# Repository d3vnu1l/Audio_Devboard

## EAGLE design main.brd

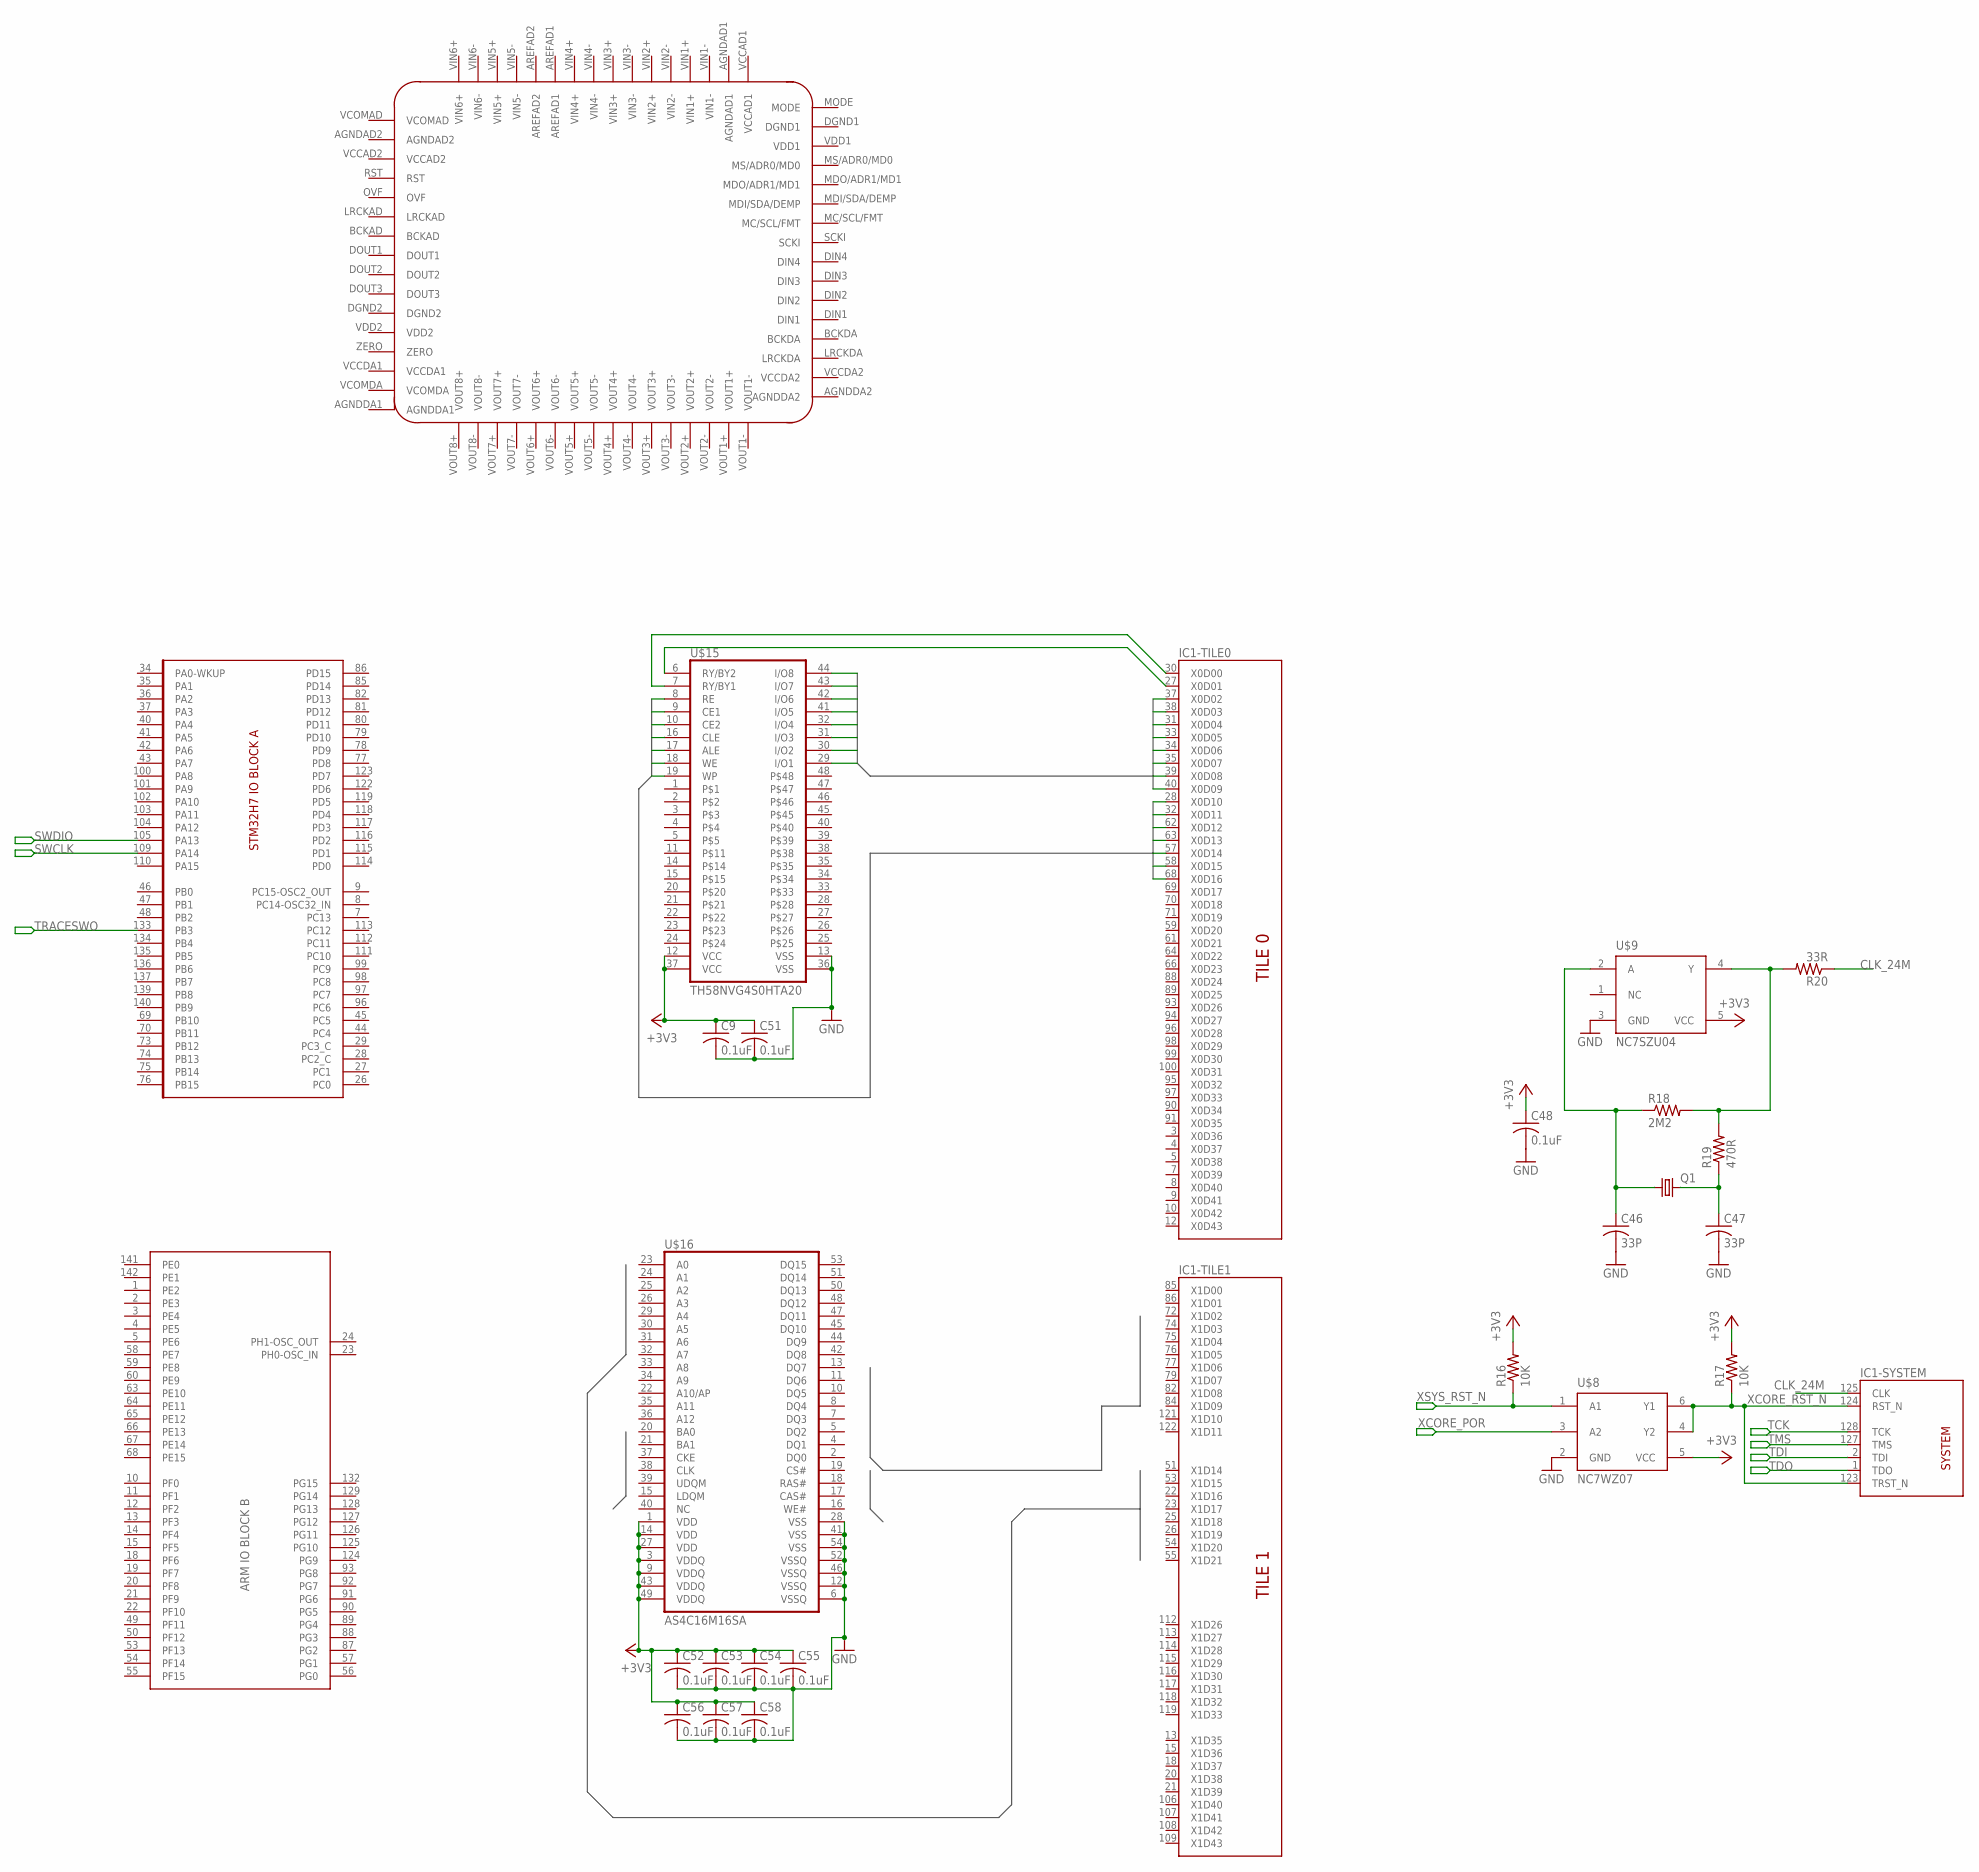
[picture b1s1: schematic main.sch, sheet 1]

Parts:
C9, C48, C51, C52, C53, C54, C55, C56, C57, C58: 0.1uF; C0603
C46, C47: 33P; C0603
IC1: XE216-TQ128; TQ128
Q1: CRYSTALSM49; SM49
R16, R17: 10K; R0603
R18: 2M2; R0603
R19: 470R; R0603
R20: 33R; R0603
U$1: STM32H7_MODULARIZED; LQFP144
U$3: PCM3168A; QFN-64-9X9MM
U$8: NC7WZ07; SC70-6L
U$9: NC7SZU04; SC70-5L
U$15: TH58NVG4S0HTA20; TSOP48
U$16: AS4C16M16SA; TSOPII-54

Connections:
+3V3: C9.1, C48.1, C51.1, C52.1, C53.1, C54.1, C55.1, C56.1, C57.1, C58.1, R16.2, R17.2, U$8.5 (VCC), U$9.5 (VCC), U$15.12 (VCC), U$15.37 (VCC), U$16.1 (VDD), U$16.3 (VDDQ), U$16.9 (VDDQ), U$16.14 (VDD), U$16.27 (VDD), U$16.43 (VDDQ), U$16.49 (VDDQ); also elsewhere on the board
ALE: IC1.57 (X0D14), U$15.17 (ALE)
CE1: IC1.32 (X0D11), U$15.9 (CE1)
CE2: IC1.62 (X0D12), U$15.10 (CE2)
CLE: IC1.63 (X0D13), U$15.16 (CLE)
CLK_24M: IC1.125 (CLK), R20.1
FLASH_BUS1: IC1.37 (X0D02), U$15.29 (I/O1)
FLASH_BUS2: IC1.38 (X0D03), U$15.30 (I/O2)
FLASH_BUS3: IC1.31 (X0D04), U$15.31 (I/O3)
FLASH_BUS4: IC1.33 (X0D05), U$15.32 (I/O4)
FLASH_BUS5: IC1.34 (X0D06), U$15.41 (I/O5)
FLASH_BUS6: IC1.35 (X0D07), U$15.42 (I/O6)
FLASH_BUS7: IC1.39 (X0D08), U$15.43 (I/O7)
FLASH_BUS8: IC1.40 (X0D09), U$15.44 (I/O8)
GND: C9.2, C46.2, C47.2, C48.2, C51.2, C52.2, C53.2, C54.2, C55.2, C56.2, C57.2, C58.2, U$8.2 (GND), U$9.3 (GND), U$15.13 (VSS), U$15.36 (VSS), U$16.6 (VSSQ), U$16.12 (VSSQ), U$16.28 (VSS), U$16.41 (VSS), U$16.46 (VSSQ), U$16.52 (VSSQ), U$16.54 (VSS); also elsewhere on the board
unnamed: C46.1, Q1.1, R18.1, U$9.2 (A)
unnamed: R18.2, R19.2, R20.2, U$9.4 (Y)
unnamed: C47.1, Q1.2, R19.1
unnamed: IC1.27 (X0D01), U$15.6 (RY/BY2)
unnamed: IC1.30 (X0D00), U$15.7 (RY/BY1)
RE: IC1.28 (X0D10), U$15.8 (RE)
SWCLK: U$1.109 (PA14); also elsewhere on the board
SWDIO: U$1.105 (PA13); also elsewhere on the board
TCK: IC1.128 (TCK); also elsewhere on the board
TDI: IC1.2 (TDI); also elsewhere on the board
TDO: IC1.1 (TDO); also elsewhere on the board
TMS: IC1.127 (TMS); also elsewhere on the board
TRACESWO: U$1.133 (PB3); also elsewhere on the board
WE: IC1.58 (X0D15), U$15.18 (WE)
WP: IC1.68 (X0D16), U$15.19 (WP)
XCORE_POR: U$8.3 (A2); also elsewhere on the board
XCORE_RST_N: IC1.123 (TRST_N), IC1.124 (RST_N), R17.1, U$8.4 (Y2), U$8.6 (Y1)
XSYS_RST_N: R16.1, U$8.1 (A1); also elsewhere on the board

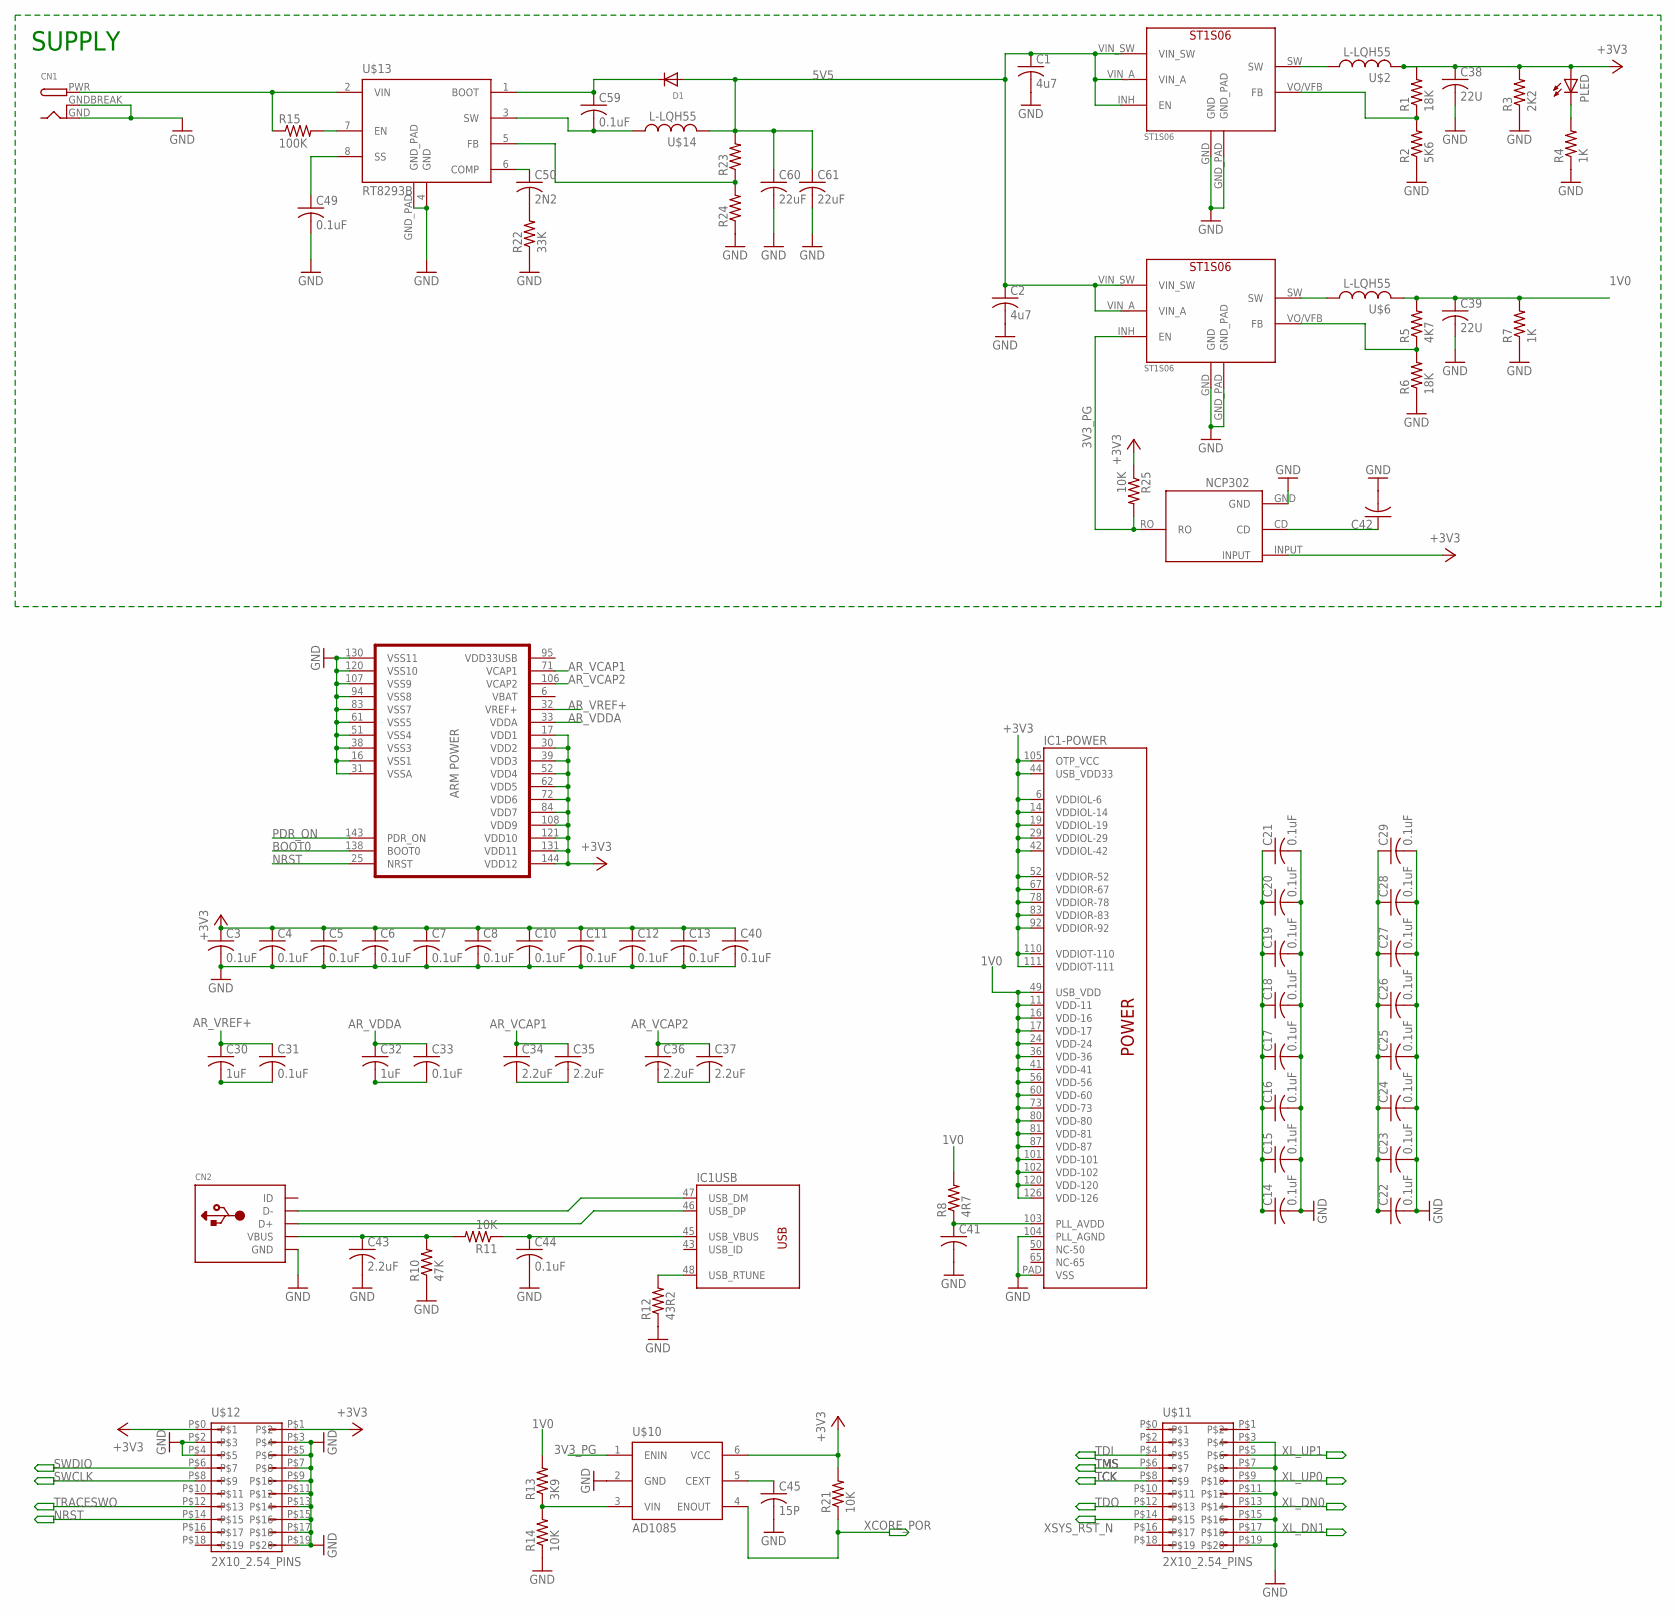
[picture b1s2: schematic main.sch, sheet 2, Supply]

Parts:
C1, C2: 4u7; C1206
C3, C4, C5, C6, C7, C8, C10, C11, C12, C13, C14, C15, C16, C17, C18, C19, C20, C21, C22, C23, C24, C25, C26, C27, C28, C29, C31, C33, C40, C44, C49, C59: 0.1uF; C0603
C30, C32: 1uF; C0603
C34, C35, C36, C37, C43: 2.2uF; C1206
C38, C39: 22U; C1206
C41, C42: C-USC0603; C0603
C45: 15P; C0603
C50: 2N2; C0603
C60, C61: 22uF; C1206
CN1: DCBARRELPTH; DCJACK_2MM_PTH
CN2: USBMINIB; USB-MINIB
D1: DIODESMA; SMADIODE
IC1: XE216-TQ128; TQ128
PLED: LEDCHIPLED_1206; CHIPLED_1206
R1, R6: 18K; R0603
R2: 5K6; R0603
R3: 2K2; R0603
R4, R7: 1K; R0603
R5: 4K7; R0603
R8: 4R7; R0603
R10: 47K; R0603
R11, R14, R21, R25: 10K; R0603
R12: 43R2; R0603
R13: 3K9; R0603
R15: 100K; R0603
R22: 33K; R0603
R23, R24: R-US_R0603; R0603
U$1: STM32H7_MODULARIZED; LQFP144
U$2, U$6, U$14: L-LQH55; LQH55
U$4, U$5: ST1S06; DFN-6
U$7: NCP302
U$10: AD1085; SC70-6L
U$11, U$12: 2X10_2.54_PINS; 2X10_2.54
U$13: RT8293B; SO-08-EP

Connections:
1V0: C39.1, IC1.11 (VDD-11), IC1.16 (VDD-16), IC1.17 (VDD-17), IC1.24 (VDD-24), IC1.36 (VDD-36), IC1.41 (VDD-41), IC1.49 (USB_VDD), IC1.56 (VDD-56), IC1.60 (VDD-60), IC1.73 (VDD-73), IC1.80 (VDD-80), IC1.81 (VDD-81), IC1.87 (VDD-87), IC1.101 (VDD-101), IC1.102 (VDD-102), IC1.120 (VDD-120), IC1.126 (VDD-126), R5.2, R7.2, R8.2, R13.2, U$6.2
3V3_PG: R25.2, U$5.INH (EN), U$7.RO, U$10.1 (ENIN)
5V5: C1.1, C2.1, C60.1, C61.1, D1.A, R23.2, U$4.INH (EN), U$4.VIN_A, U$4.VIN_SW, U$5.VIN_A, U$5.VIN_SW, U$14.2
+3V3: C3.1, C4.1, C5.1, C6.1, C7.1, C8.1, C10.1, C11.1, C12.1, C13.1, C38.1, C40.1, IC1.6 (VDDIOL-6), IC1.14 (VDDIOL-14), IC1.19 (VDDIOL-19), IC1.29 (VDDIOL-29), IC1.42 (VDDIOL-42), IC1.44 (USB_VDD33), IC1.52 (VDDIOR-52), IC1.67 (VDDIOR-67), IC1.78 (VDDIOR-78), IC1.83 (VDDIOR-83), IC1.92 (VDDIOR-92), IC1.105 (OTP_VCC), IC1.110 (VDDIOT-110), IC1.111 (VDDIOT-111), PLED.A, R1.2, R3.2, R21.2, R25.1, U$1.17 (VDD1), U$1.30 (VDD2), U$1.39 (VDD3), U$1.52 (VDD4), U$1.62 (VDD5), U$1.72 (VDD6), U$1.84 (VDD7), U$1.108 (VDD9), U$1.121 (VDD10), U$1.131 (VDD11), U$1.144 (VDD12), U$2.2, U$7.INPUT, U$10.6 (VCC), U$12.P$0, U$12.P$1; also elsewhere on the board
AR_VCAP1: C34.1, C35.1, U$1.71 (VCAP1)
AR_VCAP2: C36.1, C37.1, U$1.106 (VCAP2)
AR_VDDA: C32.1, C33.1, U$1.33 (VDDA)
AR_VREF+: C30.1, C31.1, U$1.32 (VREF+)
BOOT: C59.1, D1.C, U$13.1 (BOOT)
BOOT0: U$1.138 (BOOT0)
COMP: C50.1, U$13.6 (COMP)
EN: R15.2, U$13.7 (EN)
FB: R23.1, R24.2, U$13.5 (FB)
GND: C1.2, C2.2, C3.2, C4.2, C5.2, C6.2, C7.2, C8.2, C10.2, C11.2, C12.2, C13.2, C14.2, C15.2, C16.2, C17.2, C18.2, C19.2, C20.2, C21.2, C22.2, C23.2, C24.2, C25.2, C26.2, C27.2, C28.2, C29.2, C38.2, C39.2, C40.2, C41.2, C42.2, C43.2, C44.2, C45.2, C49.2, C60.2, C61.2, CN1.GND, CN1.GNDBREAK, CN2.GND, IC1.104 (PLL_AGND), IC1.PAD (VSS), R2.1, R3.1, R4.1, R6.1, R7.1, R10.1, R12.1, R14.1, R22.1, R24.1, U$1.16 (VSS1), U$1.31 (VSSA), U$1.38 (VSS3), U$1.51 (VSS4), U$1.61 (VSS5), U$1.83 (VSS7), U$1.94 (VSS8), U$1.107 (VSS9), U$1.120 (VSS10), U$1.130 (VSS11), U$4.GND, U$4.GND_PAD, U$5.GND, U$5.GND_PAD, U$7.GND, U$10.2 (GND), U$11.P$3, U$11.P$7, U$11.P$11, U$11.P$15, U$11.P$19, U$12.P$2, U$12.P$3, U$12.P$4, U$12.P$5, U$12.P$7, U$12.P$9, U$12.P$11, U$12.P$13, U$12.P$15, U$12.P$17, U$12.P$19, U$13.4 (GND), U$13.GND_PAD; also elsewhere on the board
unnamed: C14.1, C15.1, C16.1, C17.1, C18.1, C19.1, C20.1, C21.1
unnamed: C41.1, IC1.103 (PLL_AVDD), R8.1
unnamed: C42.1, U$7.CD
unnamed: C43.1, CN2.VBUS, R10.2, R11.2
unnamed: C34.2, C35.2
unnamed: C22.1, C23.1, C24.1, C25.1, C26.1, C27.1, C28.1, C29.1
unnamed: C36.2, C37.2
unnamed: C44.1, IC1.45 (USB_VBUS), R11.1
unnamed: C32.2, C33.2
unnamed: C30.2, C31.2
unnamed: IC1.48 (USB_RTUNE), R12.2
unnamed: CN2.D+, IC1.46 (USB_DP)
unnamed: CN2.D-, IC1.47 (USB_DM)
unnamed: PLED.C, R4.2
unnamed: R1.1, R2.2, U$4.VO/VFB (FB)
unnamed: R5.1, R6.2, U$5.VO/VFB (FB)
unnamed: U$2.1, U$4.SW
unnamed: U$5.SW, U$6.1
unnamed: R13.1, R14.2, U$10.3 (VIN)
unnamed: C45.1, U$10.5 (CEXT)
unnamed: C50.2, R22.2
NRST: U$1.25 (NRST), U$12.P$14
PDR_ON: U$1.143 (PDR_ON)
PWR: CN1.PWR, R15.1, U$13.2 (VIN)
SS: C49.1, U$13.8 (SS)
SW: C59.2, U$13.3 (SW), U$14.1
SWCLK: U$12.P$8; also elsewhere on the board
SWDIO: U$12.P$6; also elsewhere on the board
TCK: U$11.P$8; also elsewhere on the board
TDI: U$11.P$4; also elsewhere on the board
TDO: U$11.P$12; also elsewhere on the board
TMS: U$11.P$6; also elsewhere on the board
TRACESWO: U$12.P$12; also elsewhere on the board
XCORE_POR: R21.1, U$10.4 (ENOUT); also elsewhere on the board
XL_DN0: U$11.P$13
XL_DN1: U$11.P$17
XL_UP0: U$11.P$9
XL_UP1: U$11.P$5
XSYS_RST_N: U$11.P$14; also elsewhere on the board

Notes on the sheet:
SUPPLY

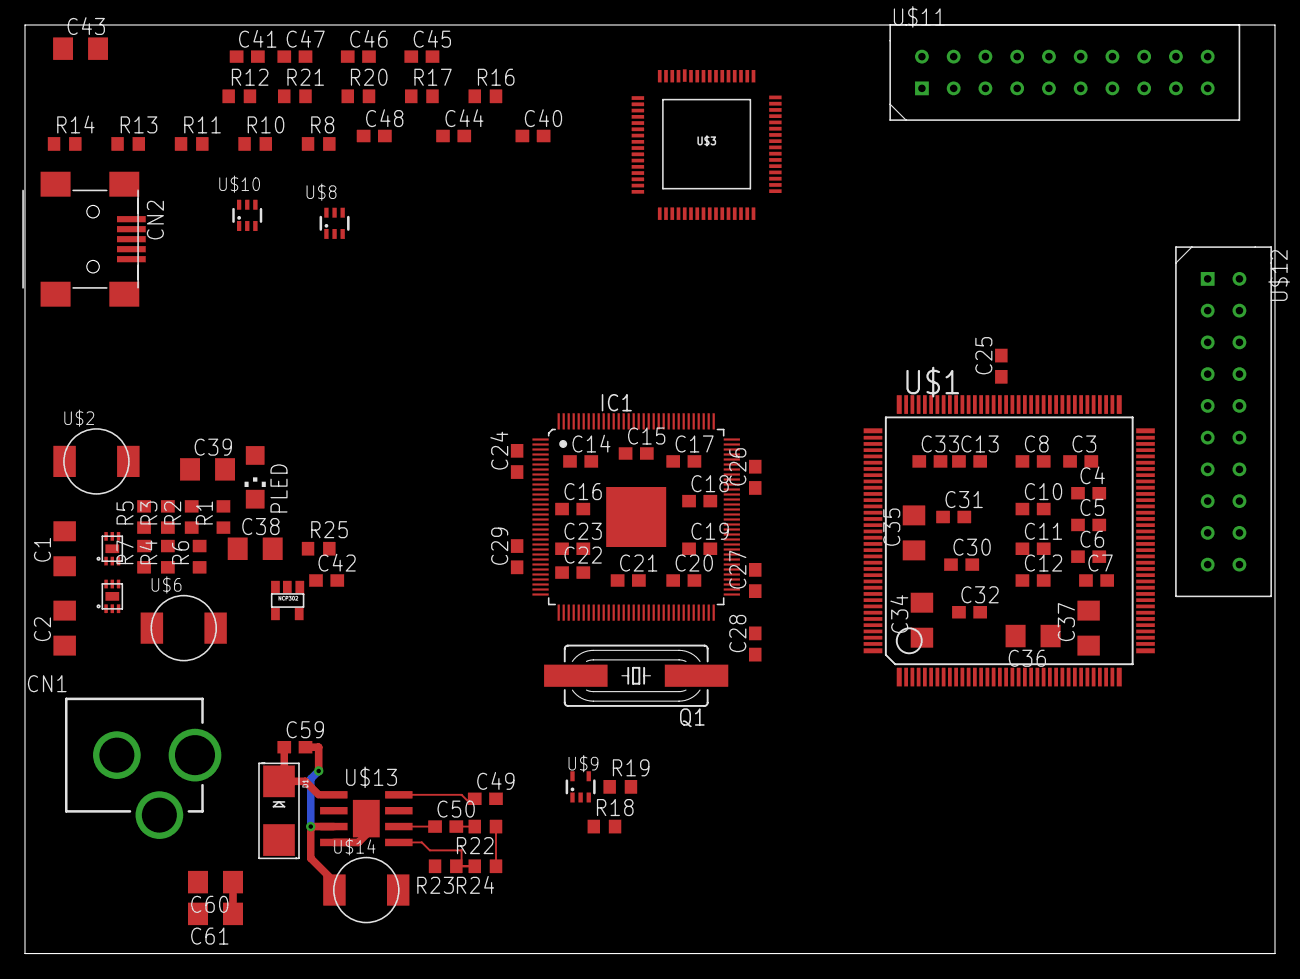
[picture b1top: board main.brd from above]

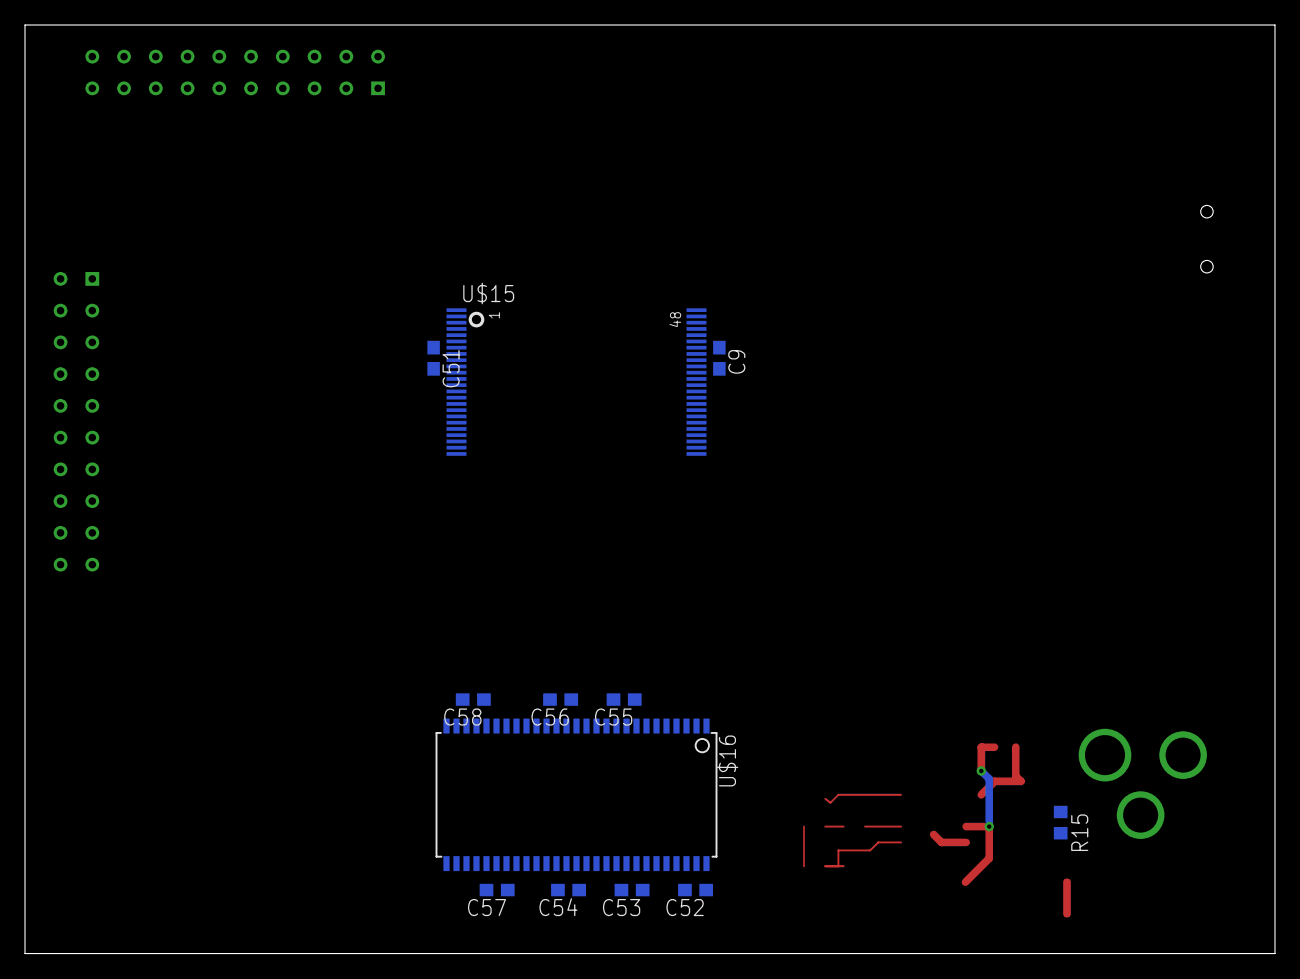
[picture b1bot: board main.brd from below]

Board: 2 copper layers, 100.0 x 74.3 mm, 107 parts (12 on the bottom side), 69 nets.

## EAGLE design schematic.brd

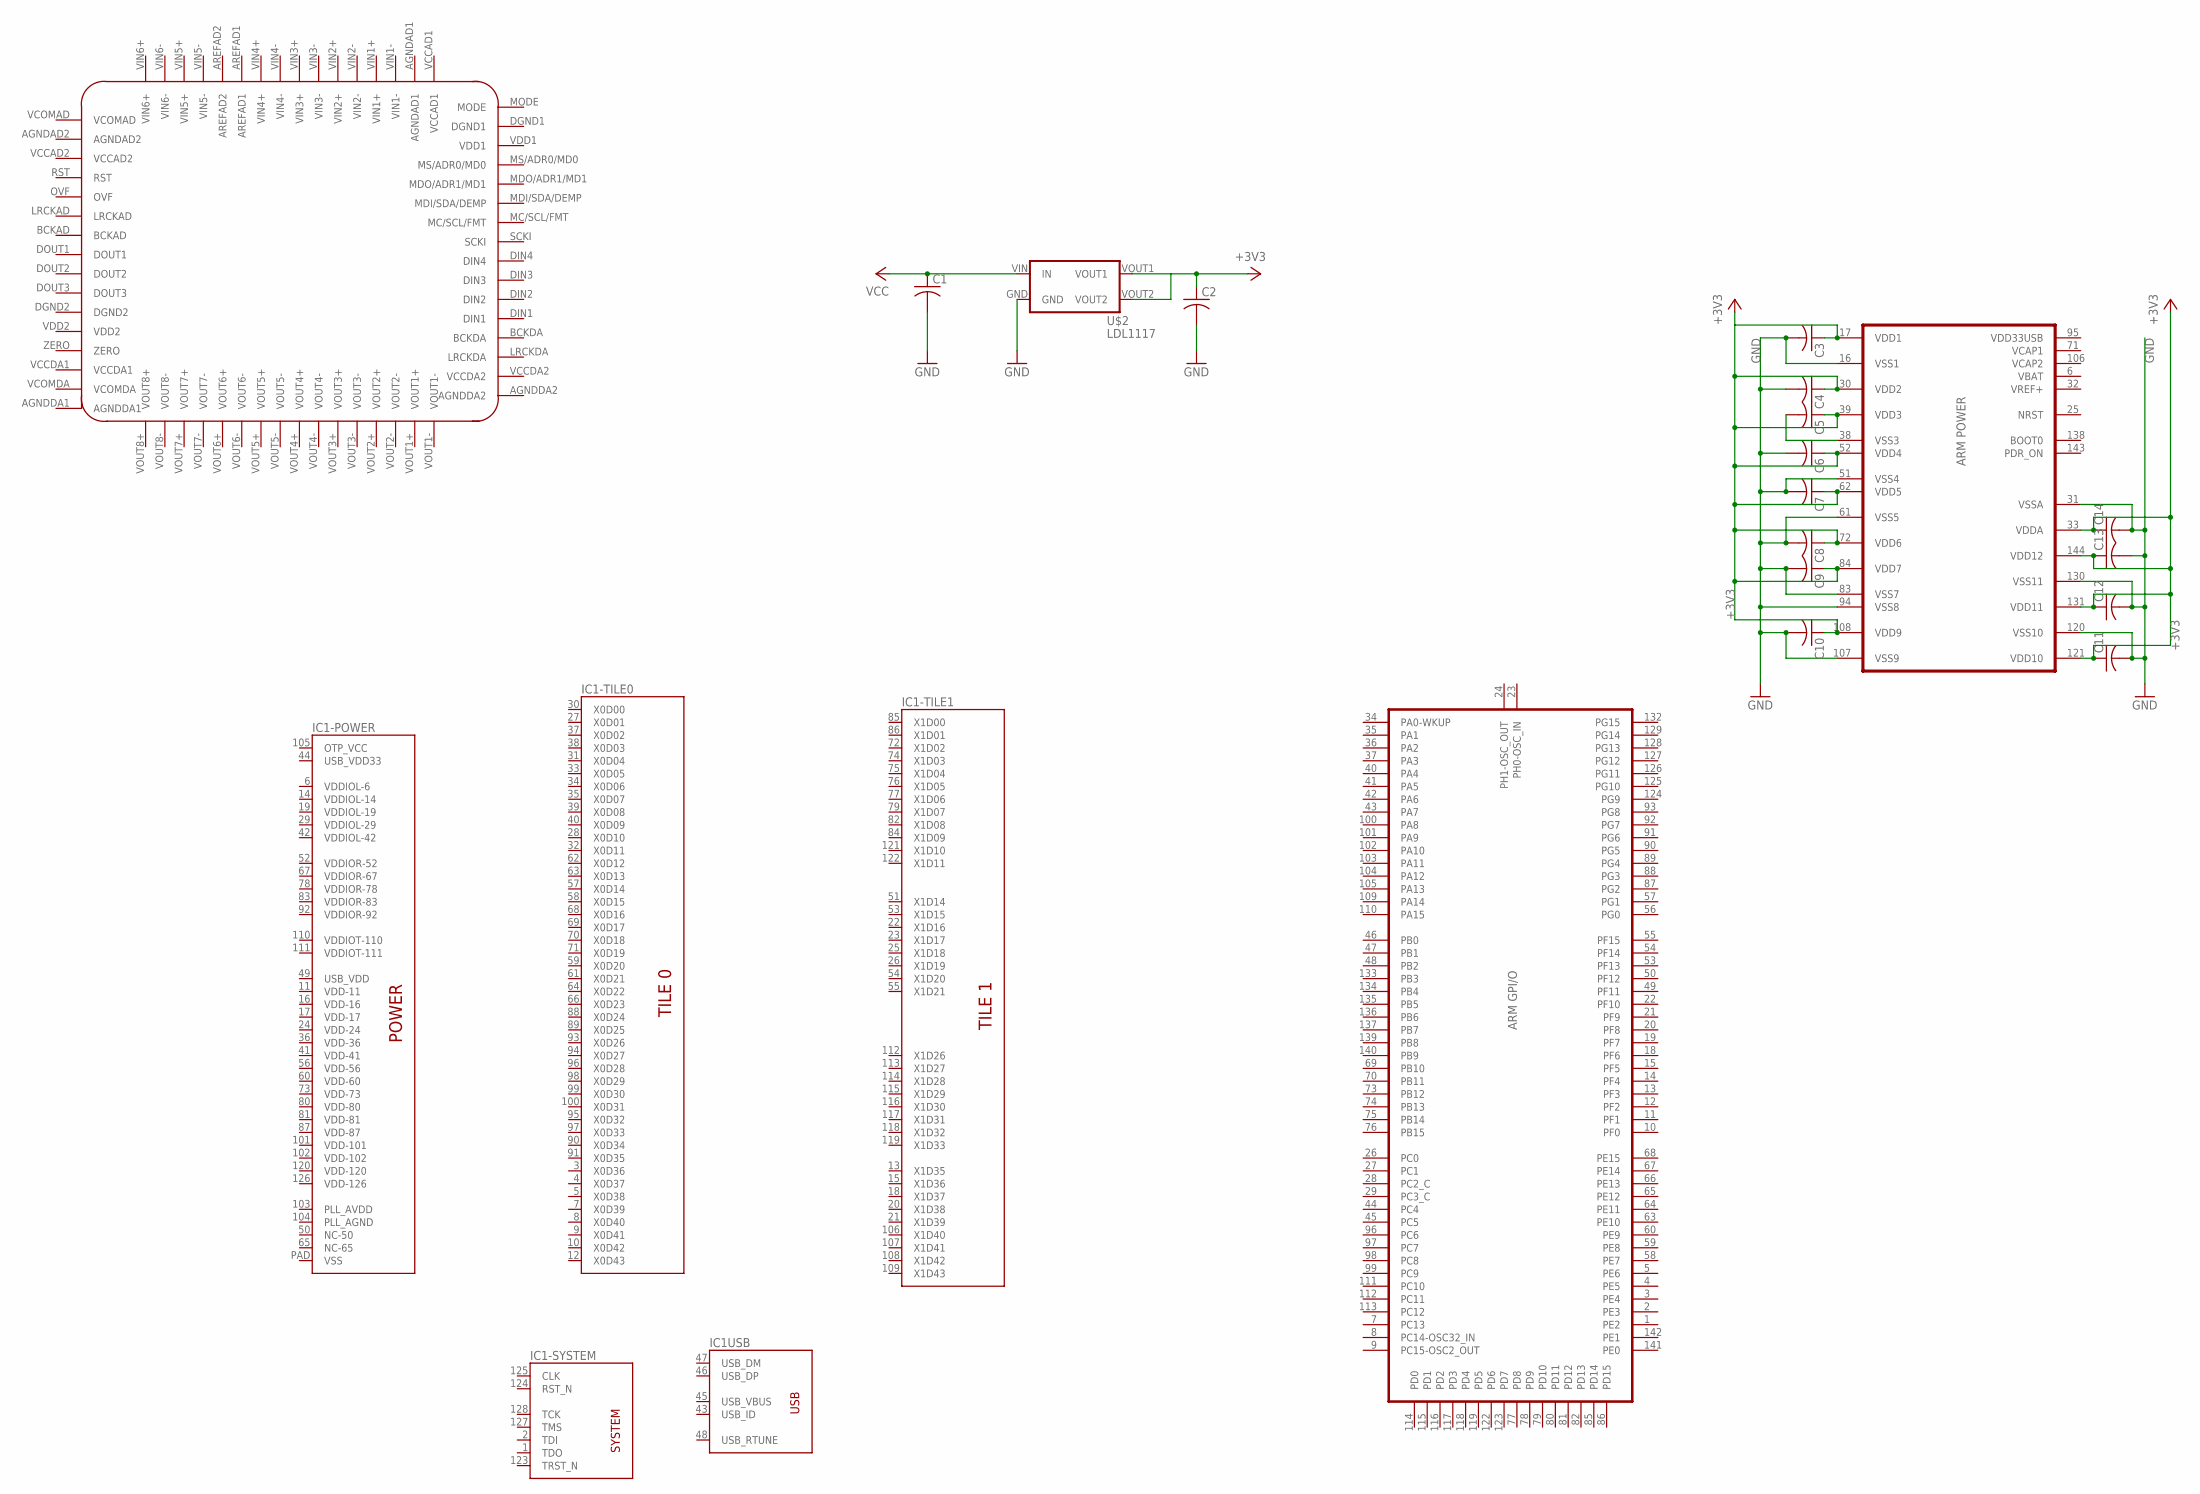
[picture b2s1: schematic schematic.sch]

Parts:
C1, C3, C4, C5, C6, C7, C8, C9, C10, C11, C12, C13, C14: C-USC0603; C0603
C2: C-USC1206; C1206
IC1: XE216-TQ128; TQ128
U$1: STM32H743ZIT6; LQFP144
U$2: LDL1117; SOT223
U$3: PCM3168A; QFN-64-9X9MM

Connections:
+3V3: C2.1, C3.1, C4.1, C5.1, C6.1, C7.1, C8.1, C9.1, C10.1, C11.1, C12.1, C13.1, C14.1, U$1.17 (VDD1), U$1.30 (VDD2), U$1.33 (VDDA), U$1.39 (VDD3), U$1.52 (VDD4), U$1.62 (VDD5), U$1.72 (VDD6), U$1.84 (VDD7), U$1.108 (VDD9), U$1.121 (VDD10), U$1.131 (VDD11), U$1.144 (VDD12), U$2.VOUT1
GND: C1.2, C2.2, C3.2, C4.2, C6.2, C7.2, C8.2, C9.2, C10.2, C11.2, C12.2, C13.2, C14.2, U$1.16 (VSS1), U$1.31 (VSSA), U$1.51 (VSS4), U$1.61 (VSS5), U$1.83 (VSS7), U$1.94 (VSS8), U$1.107 (VSS9), U$1.120 (VSS10), U$1.130 (VSS11), U$2.GND
unnamed: C5.2, U$1.38 (VSS3)
OTP_VCC: IC1.105 (OTP_VCC)
PLL_AGND: IC1.104 (PLL_AGND)
PLL_AVDD: IC1.103 (PLL_AVDD)
USB_VDD: IC1.49 (USB_VDD)
USB_VDD33: IC1.44 (USB_VDD33)
VCC: C1.1, U$2.VIN (IN)
VDD-11: IC1.11 (VDD-11)
VDD-16: IC1.16 (VDD-16)
VDD-17: IC1.17 (VDD-17)
VDD-24: IC1.24 (VDD-24)
VDD-36: IC1.36 (VDD-36)
VDD-41: IC1.41 (VDD-41)
VDD-56: IC1.56 (VDD-56)
VDD-60: IC1.60 (VDD-60)
VDD-73: IC1.73 (VDD-73)
VDD-80: IC1.80 (VDD-80)
VDD-81: IC1.81 (VDD-81)
VDD-87: IC1.87 (VDD-87)
VDD-101: IC1.101 (VDD-101)
VDD-102: IC1.102 (VDD-102)
VDD-120: IC1.120 (VDD-120)
VDD-126: IC1.126 (VDD-126)
VDDIOL-6: IC1.6 (VDDIOL-6)
VDDIOL-14: IC1.14 (VDDIOL-14)
VDDIOL-19: IC1.19 (VDDIOL-19)
VDDIOL-29: IC1.29 (VDDIOL-29)
VDDIOL-42: IC1.42 (VDDIOL-42)
VDDIOR-52: IC1.52 (VDDIOR-52)
VDDIOR-67: IC1.67 (VDDIOR-67)
VDDIOR-78: IC1.78 (VDDIOR-78)
VDDIOR-83: IC1.83 (VDDIOR-83)
VDDIOR-92: IC1.92 (VDDIOR-92)
VDDIOT-110: IC1.110 (VDDIOT-110)
VDDIOT-111: IC1.111 (VDDIOT-111)
VSS: IC1.PAD (VSS)

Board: 2 copper layers, 18 parts (0 on the bottom side), 4 nets, no tracks yet.

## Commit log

2018-03-01 Added schematic and project files
2018-03-01 Added a board file
2018-03-01 Partially connected ARM power
    need to add additional caps for analog power. Using 0603 for <=1uf and 1206 for >1uf
2018-03-01 Separated arm symbol into blocks. Multiple schematics for power and digital now.
2018-03-01 accidentally removed schematic
2018-03-01 remove old unused files
2018-03-04 Add program Headers. PSU almost done.
2018-03-04 Update psu to 12v. Added memory chips.
2018-03-05 Added some busses for memory chips
